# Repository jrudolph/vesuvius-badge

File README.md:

# Vesuvius First Word Badge - Hardware Design Files (for Kicad)

This repository contains the hardware design files for the Vesuvius First Word Badge badge that displays the first word found in burnt papyrus scrolls
analyzed for the [Vesuvius Challenge](https://scrollprize.substack.com/p/first-word-discovered-in-unopened).

Read more about the hardware of the badge in this [blog post](https://vesuvius.virtual-void.net/blog/2024/01/10/vesuvius-badge-hardware/). The Pico-based
firmware can be found in [vesuvius-badge-pico](https://github.com/jrudolph/vesuvius-badge-pico).

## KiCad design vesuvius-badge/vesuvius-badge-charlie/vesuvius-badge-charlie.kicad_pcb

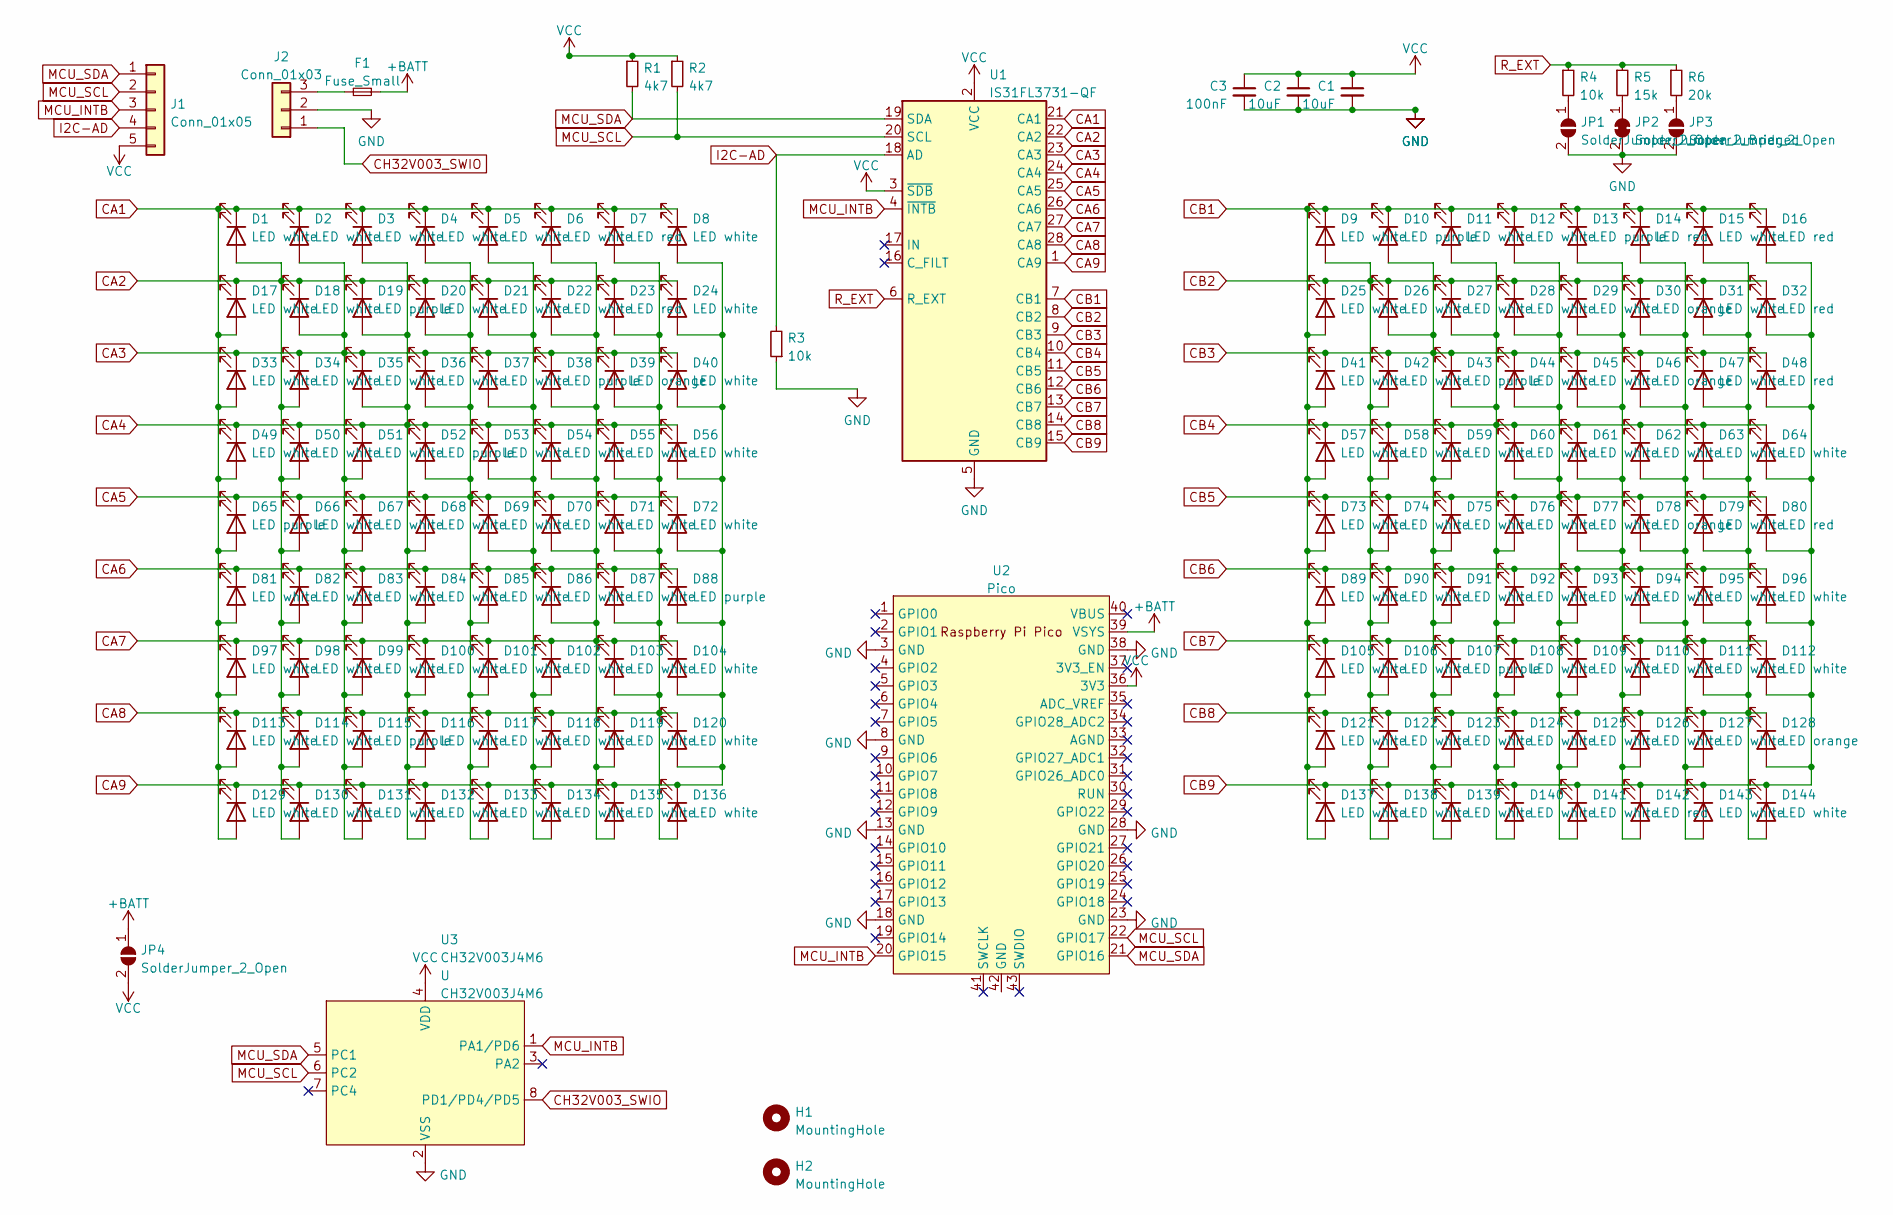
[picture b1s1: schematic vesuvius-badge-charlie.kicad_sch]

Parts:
C1, C2: 10uF; C_0402_1005Metric; LCSC C15525
C3: 100nF; C_0402_1005Metric; LCSC C1525
D1, D2, D3, D4, D5, D6, D8, D9, D11, D12, D15, D17, D18, D20, D21, D22, D24, D25, D26, D27, D28, D29, D31, D33, D34, D35, D36, D37, D40, D41, D42, D44, D45, D47, D49, D50, D51, D53, D54, D55, D56, D57, D58, D59, D60, D61, D62, D63, D64, D66, D67, D68, D69, D70, D71, D72, D73, D74, D75, D76, D77, D79, D81, D82, D83, D84, D85, D86, D87, D89, D90, D91, D92, D93, D94, D95, D96, D97, D98, D99, D100, D101, D102, D103, D104, D105, D106, D108, D109, D110, D111, D112, D113, D114, D116, D117, D118, D119, D120, D121, D122, D123, D124, D125, D126, D127, D129, D130, D131, D132, D133, D134, D135, D136, D137, D138, D139, D140, D141, D143, D144: LED white; LED_0402_1005Metric; LCSC C965796
D7, D14, D16, D23, D32, D48, D80, D142: LED red; LED_0402_1005Metric; LCSC C779449
D10, D13, D19, D38, D43, D52, D65, D88, D107, D115: LED purple; LED_0603_1608Metric; LCSC C7371898
D30, D39, D46, D78, D128: LED orange; LED_0402_1005Metric; LCSC C779448
F1: Fuse_Small; Fuse_0402_1005Metric; LCSC C136320
H1, H2: MountingHole; MountingHole_5.3mm_M5
J1: Conn_01x05; PinHeader_1x05_P2.54mm_Vertical
J2: Conn_01x03; PinHeader_1x03_P2.54mm_Vertical
JP1, JP3, JP4: SolderJumper_2_Open; SolderJumper-2_P1.3mm_Open_Pad1.0x1.5mm
JP2: SolderJumper_2_Bridged; SolderJumper-2_P1.3mm_Bridged_Pad1.0x1.5mm
R1, R2: 4k7; R_0603_1608Metric; LCSC C23162
R3, R4: 10k; R_0603_1608Metric; LCSC C25804
R5: 15k; R_0603_1608Metric; LCSC C22809
R6: 20k; R_0603_1608Metric; LCSC C4184
U1: IS31FL3731-QF; QFN-28-1EP_4x4mm_P0.4mm_EP2.3x2.3mm; LCSC C191206
U2: Pico; RPi_Pico_SMD
U3: CH32V003J4M6; SOP-8_3.9x4.9mm_P1.27mm

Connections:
+BATT: F1.2, JP4.1 (A), U2.39 (VSYS)
CA1: D1.1 (K), D2.1 (K), D3.1 (K), D4.1 (K), D5.1 (K), D6.1 (K), D7.1 (K), D8.1 (K), D17.2 (A), D33.2 (A), D49.2 (A), D65.2 (A), D81.2 (A), D97.2 (A), D113.2 (A), D129.2 (A), U1.21 (CA1)
CA2: D1.2 (A), D17.1 (K), D18.1 (K), D19.1 (K), D20.1 (K), D21.1 (K), D22.1 (K), D23.1 (K), D24.1 (K), D34.2 (A), D50.2 (A), D66.2 (A), D82.2 (A), D98.2 (A), D114.2 (A), D130.2 (A), U1.22 (CA2)
CA3: D2.2 (A), D18.2 (A), D33.1 (K), D34.1 (K), D35.1 (K), D36.1 (K), D37.1 (K), D38.1 (K), D39.1 (K), D40.1 (K), D51.2 (A), D67.2 (A), D83.2 (A), D99.2 (A), D115.2 (A), D131.2 (A), U1.23 (CA3)
CA4: D3.2 (A), D19.2 (A), D35.2 (A), D49.1 (K), D50.1 (K), D51.1 (K), D52.1 (K), D53.1 (K), D54.1 (K), D55.1 (K), D56.1 (K), D68.2 (A), D84.2 (A), D100.2 (A), D116.2 (A), D132.2 (A), U1.24 (CA4)
CA5: D4.2 (A), D20.2 (A), D36.2 (A), D52.2 (A), D65.1 (K), D66.1 (K), D67.1 (K), D68.1 (K), D69.1 (K), D70.1 (K), D71.1 (K), D72.1 (K), D85.2 (A), D101.2 (A), D117.2 (A), D133.2 (A), U1.25 (CA5)
CA6: D5.2 (A), D21.2 (A), D37.2 (A), D53.2 (A), D69.2 (A), D81.1 (K), D82.1 (K), D83.1 (K), D84.1 (K), D85.1 (K), D86.1 (K), D87.1 (K), D88.1 (K), D102.2 (A), D118.2 (A), D134.2 (A), U1.26 (CA6)
CA7: D6.2 (A), D22.2 (A), D38.2 (A), D54.2 (A), D70.2 (A), D86.2 (A), D97.1 (K), D98.1 (K), D99.1 (K), D100.1 (K), D101.1 (K), D102.1 (K), D103.1 (K), D104.1 (K), D119.2 (A), D135.2 (A), U1.27 (CA7)
CA8: D7.2 (A), D23.2 (A), D39.2 (A), D55.2 (A), D71.2 (A), D87.2 (A), D103.2 (A), D113.1 (K), D114.1 (K), D115.1 (K), D116.1 (K), D117.1 (K), D118.1 (K), D119.1 (K), D120.1 (K), D136.2 (A), U1.28 (CA8)
CA9: D8.2 (A), D24.2 (A), D40.2 (A), D56.2 (A), D72.2 (A), D88.2 (A), D104.2 (A), D120.2 (A), D129.1 (K), D130.1 (K), D131.1 (K), D132.1 (K), D133.1 (K), D134.1 (K), D135.1 (K), D136.1 (K), U1.1 (CA9)
CB1: D9.1 (K), D10.1 (K), D11.1 (K), D12.1 (K), D13.1 (K), D14.1 (K), D15.1 (K), D16.1 (K), D25.2 (A), D41.2 (A), D57.2 (A), D73.2 (A), D89.2 (A), D105.2 (A), D121.2 (A), D137.2 (A), U1.7 (CB1)
CB2: D9.2 (A), D25.1 (K), D26.1 (K), D27.1 (K), D28.1 (K), D29.1 (K), D30.1 (K), D31.1 (K), D32.1 (K), D42.2 (A), D58.2 (A), D74.2 (A), D90.2 (A), D106.2 (A), D122.2 (A), D138.2 (A), U1.8 (CB2)
CB3: D10.2 (A), D26.2 (A), D41.1 (K), D42.1 (K), D43.1 (K), D44.1 (K), D45.1 (K), D46.1 (K), D47.1 (K), D48.1 (K), D59.2 (A), D75.2 (A), D91.2 (A), D107.2 (A), D123.2 (A), D139.2 (A), U1.9 (CB3)
CB4: D11.2 (A), D27.2 (A), D43.2 (A), D57.1 (K), D58.1 (K), D59.1 (K), D60.1 (K), D61.1 (K), D62.1 (K), D63.1 (K), D64.1 (K), D76.2 (A), D92.2 (A), D108.2 (A), D124.2 (A), D140.2 (A), U1.10 (CB4)
CB5: D12.2 (A), D28.2 (A), D44.2 (A), D60.2 (A), D73.1 (K), D74.1 (K), D75.1 (K), D76.1 (K), D77.1 (K), D78.1 (K), D79.1 (K), D80.1 (K), D93.2 (A), D109.2 (A), D125.2 (A), D141.2 (A), U1.11 (CB5)
CB6: D13.2 (A), D29.2 (A), D45.2 (A), D61.2 (A), D77.2 (A), D89.1 (K), D90.1 (K), D91.1 (K), D92.1 (K), D93.1 (K), D94.1 (K), D95.1 (K), D96.1 (K), D110.2 (A), D126.2 (A), D142.2 (A), U1.12 (CB6)
CB7: D14.2 (A), D30.2 (A), D46.2 (A), D62.2 (A), D78.2 (A), D94.2 (A), D105.1 (K), D106.1 (K), D107.1 (K), D108.1 (K), D109.1 (K), D110.1 (K), D111.1 (K), D112.1 (K), D127.2 (A), D143.2 (A), U1.13 (CB7)
CB8: D15.2 (A), D31.2 (A), D47.2 (A), D63.2 (A), D79.2 (A), D95.2 (A), D111.2 (A), D121.1 (K), D122.1 (K), D123.1 (K), D124.1 (K), D125.1 (K), D126.1 (K), D127.1 (K), D128.1 (K), D144.2 (A), U1.14 (CB8)
CB9: D16.2 (A), D32.2 (A), D48.2 (A), D64.2 (A), D80.2 (A), D96.2 (A), D112.2 (A), D128.2 (A), D137.1 (K), D138.1 (K), D139.1 (K), D140.1 (K), D141.1 (K), D142.1 (K), D143.1 (K), D144.1 (K), U1.15 (CB9)
CH32V003_SWIO: J2.1, U3.8 (PD1/PD4/PD5)
GND: C1.2, C2.2, C3.2, J2.2, JP1.2 (B), JP2.2 (B), JP3.2 (B), R3.1, U1.5 (GND), U1.29 (GND), U2.3 (GND), U2.8 (GND), U2.13 (GND), U2.18 (GND), U2.23 (GND), U2.28 (GND), U2.38 (GND), U3.2 (VSS)
I2C-AD: J1.4, R3.2, U1.18 (AD)
MCU_INTB: J1.3, U1.4 (~INTB), U2.20 (GPIO15), U3.1 (PA1/PD6)
MCU_SCL: J1.2, R2.2, U1.20 (SCL), U2.22 (GPIO17), U3.6 (PC2)
MCU_SDA: J1.1, R1.2, U1.19 (SDA), U2.21 (GPIO16), U3.5 (PC1)
unnamed: F1.1, J2.3
unnamed: JP1.1 (A), R4.2
unnamed: JP2.1 (A), R5.2
unnamed: JP3.1 (A), R6.2
R_EXT: R4.1, R5.1, R6.1, U1.6 (R_EXT)
VCC: C1.1, C2.1, C3.1, J1.5, JP4.2 (B), R1.1, R2.1, U1.2 (VCC), U1.3 (~SDB), U2.36 (3V3), U3.4 (VDD)

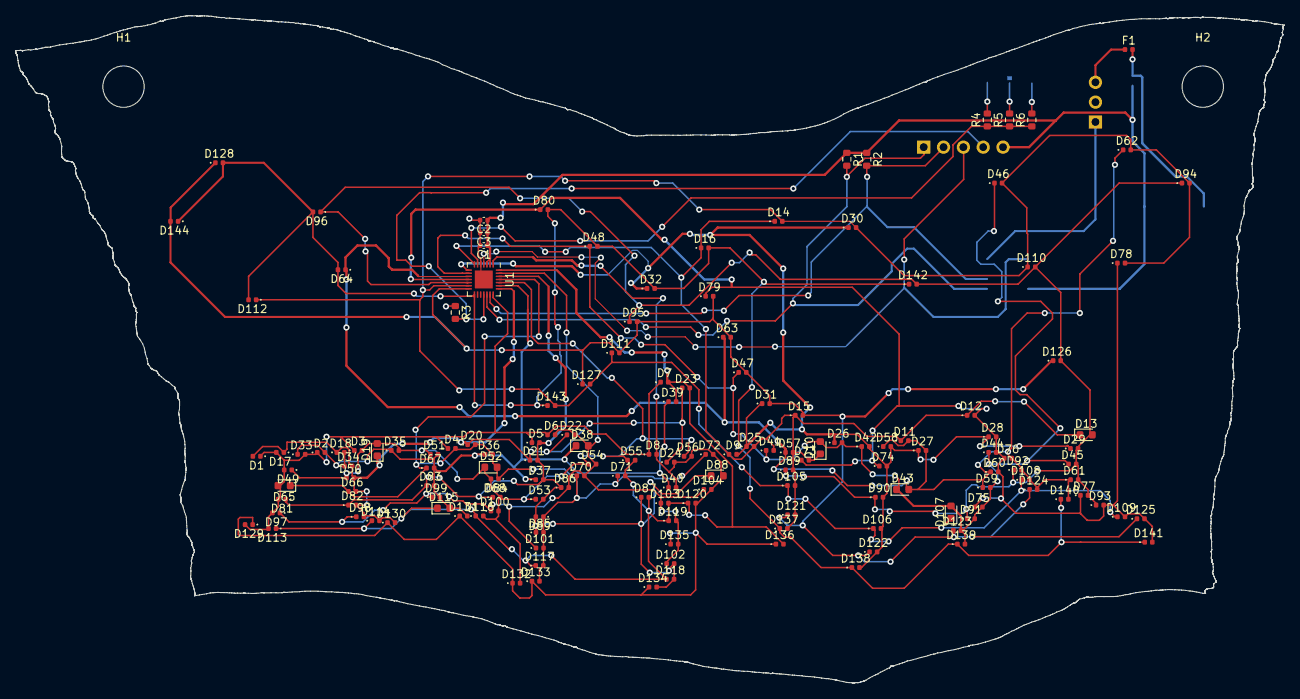
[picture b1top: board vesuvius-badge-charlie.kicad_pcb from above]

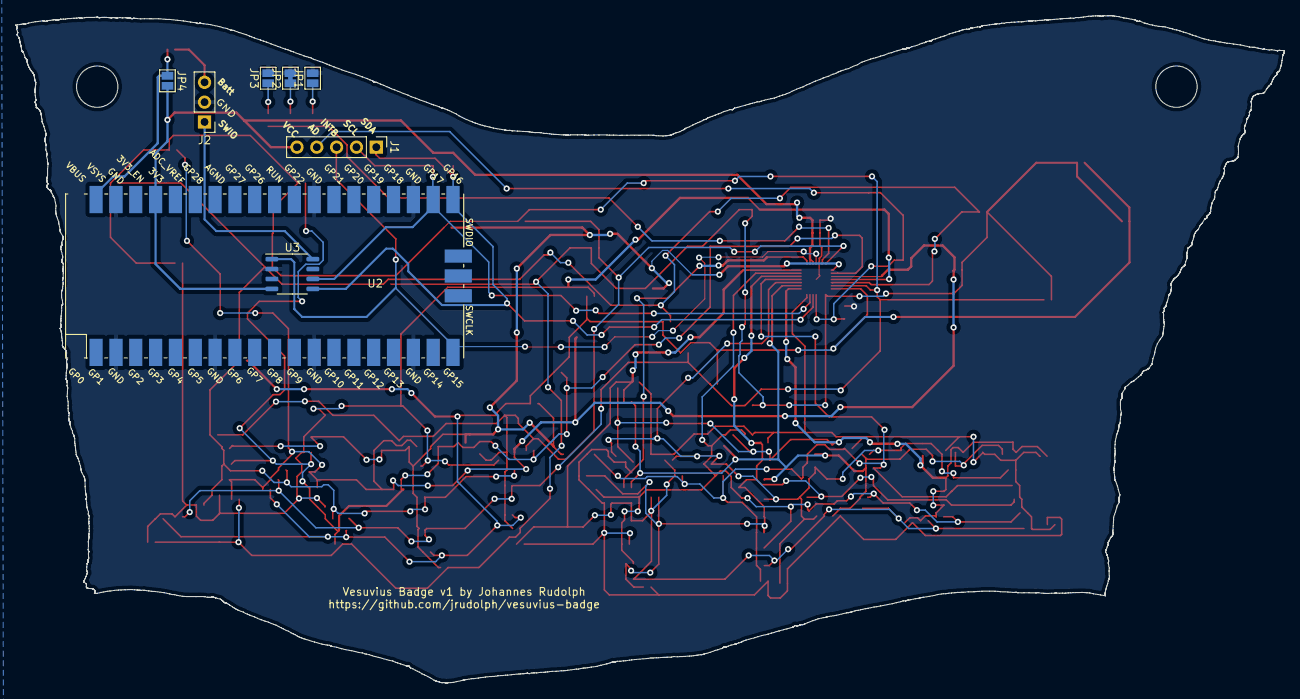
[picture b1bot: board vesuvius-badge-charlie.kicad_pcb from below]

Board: 2 copper layers, 162.5 x 85.5 mm, 165 parts (8 on the bottom side), 31 nets.

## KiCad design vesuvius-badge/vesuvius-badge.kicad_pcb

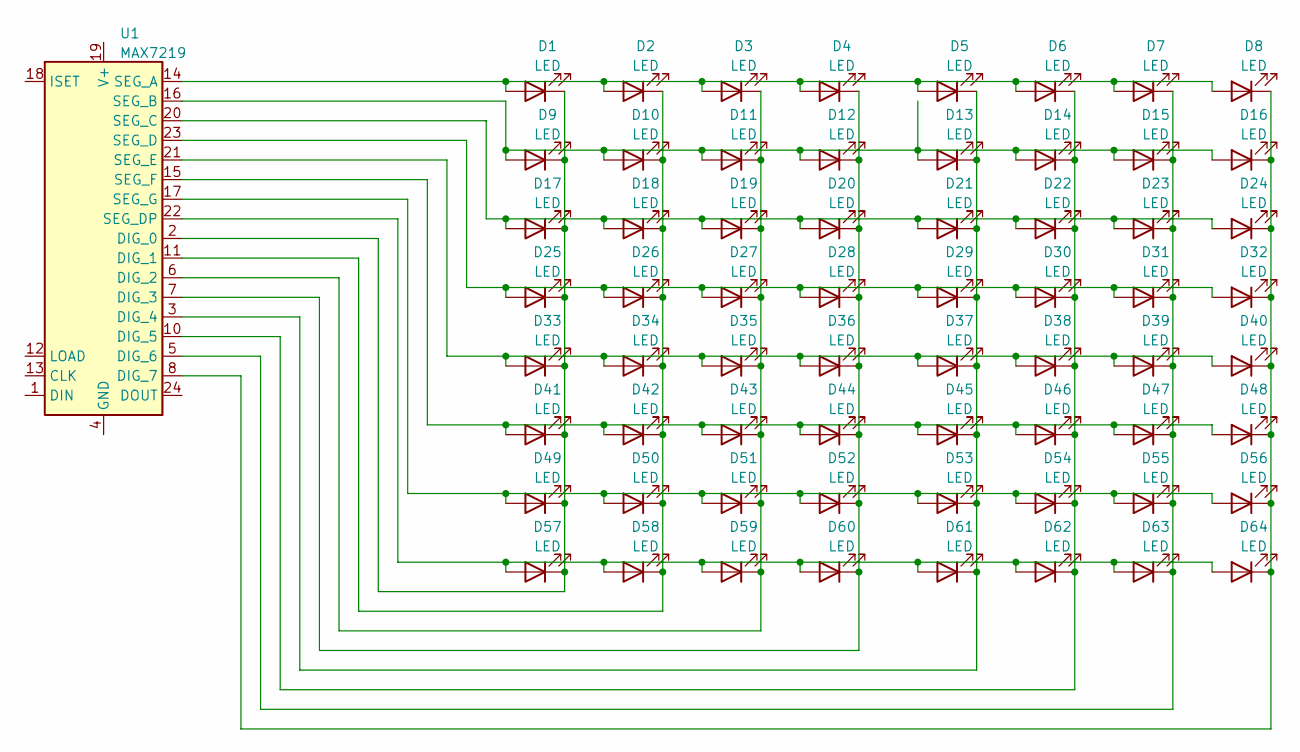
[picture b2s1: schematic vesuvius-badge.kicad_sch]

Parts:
D1, D2, D3, D4, D5, D6, D7, D8, D9, D10, D11, D12, D13, D14, D15, D16, D17, D18, D19, D20, D21, D22, D23, D24, D25, D26, D27, D28, D29, D30, D31, D32, D33, D34, D35, D36, D37, D38, D39, D40, D41, D42, D43, D44, D45, D46, D47, D48, D49, D50, D51, D52, D53, D54, D55, D56, D57, D58, D59, D60, D61, D62, D63, D64: LED; LED_0603_1608Metric
U1: MAX7219; SOP-24_7.5x15.4mm_P1.27mm

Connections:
unnamed: D1.1 (K), D9.1 (K), D17.1 (K), D25.1 (K), D33.1 (K), D41.1 (K), D49.1 (K), D57.1 (K), U1.2 (DIG_0)
unnamed: D1.2 (A), D2.2 (A), D3.2 (A), D4.2 (A), D5.2 (A), D6.2 (A), D7.2 (A), D8.2 (A), U1.14 (SEG_A)
unnamed: D2.1 (K), D10.1 (K), D18.1 (K), D26.1 (K), D34.1 (K), D42.1 (K), D50.1 (K), D58.1 (K), U1.11 (DIG_1)
unnamed: D9.2 (A), D10.2 (A), D11.2 (A), D12.2 (A), D13.2 (A), D14.2 (A), D15.2 (A), D16.2 (A), U1.16 (SEG_B)
unnamed: D3.1 (K), D11.1 (K), D19.1 (K), D27.1 (K), D35.1 (K), D43.1 (K), D51.1 (K), D59.1 (K), U1.6 (DIG_2)
unnamed: D4.1 (K), D12.1 (K), D20.1 (K), D28.1 (K), D36.1 (K), D44.1 (K), D52.1 (K), D60.1 (K), U1.7 (DIG_3)
unnamed: D5.1 (K), D13.1 (K), D21.1 (K), D29.1 (K), D37.1 (K), D45.1 (K), D53.1 (K), D61.1 (K), U1.3 (DIG_4)
unnamed: D6.1 (K), D14.1 (K), D22.1 (K), D30.1 (K), D38.1 (K), D46.1 (K), D54.1 (K), D62.1 (K), U1.10 (DIG_5)
unnamed: D7.1 (K), D15.1 (K), D23.1 (K), D31.1 (K), D39.1 (K), D47.1 (K), D55.1 (K), D63.1 (K), U1.5 (DIG_6)
unnamed: D8.1 (K), D16.1 (K), D24.1 (K), D32.1 (K), D40.1 (K), D48.1 (K), D56.1 (K), D64.1 (K), U1.8 (DIG_7)
unnamed: D17.2 (A), D18.2 (A), D19.2 (A), D20.2 (A), D21.2 (A), D22.2 (A), D23.2 (A), D24.2 (A), U1.20 (SEG_C)
unnamed: D25.2 (A), D26.2 (A), D27.2 (A), D28.2 (A), D29.2 (A), D30.2 (A), D31.2 (A), D32.2 (A), U1.23 (SEG_D)
unnamed: D33.2 (A), D34.2 (A), D35.2 (A), D36.2 (A), D37.2 (A), D38.2 (A), D39.2 (A), D40.2 (A), U1.21 (SEG_E)
unnamed: D41.2 (A), D42.2 (A), D43.2 (A), D44.2 (A), D45.2 (A), D46.2 (A), D47.2 (A), D48.2 (A), U1.15 (SEG_F)
unnamed: D49.2 (A), D50.2 (A), D51.2 (A), D52.2 (A), D53.2 (A), D54.2 (A), D55.2 (A), D56.2 (A), U1.17 (SEG_G)
unnamed: D57.2 (A), D58.2 (A), D59.2 (A), D60.2 (A), D61.2 (A), D62.2 (A), D63.2 (A), D64.2 (A), U1.22 (SEG_DP)
unnamed: U1.4 (GND), U1.9 (GND)

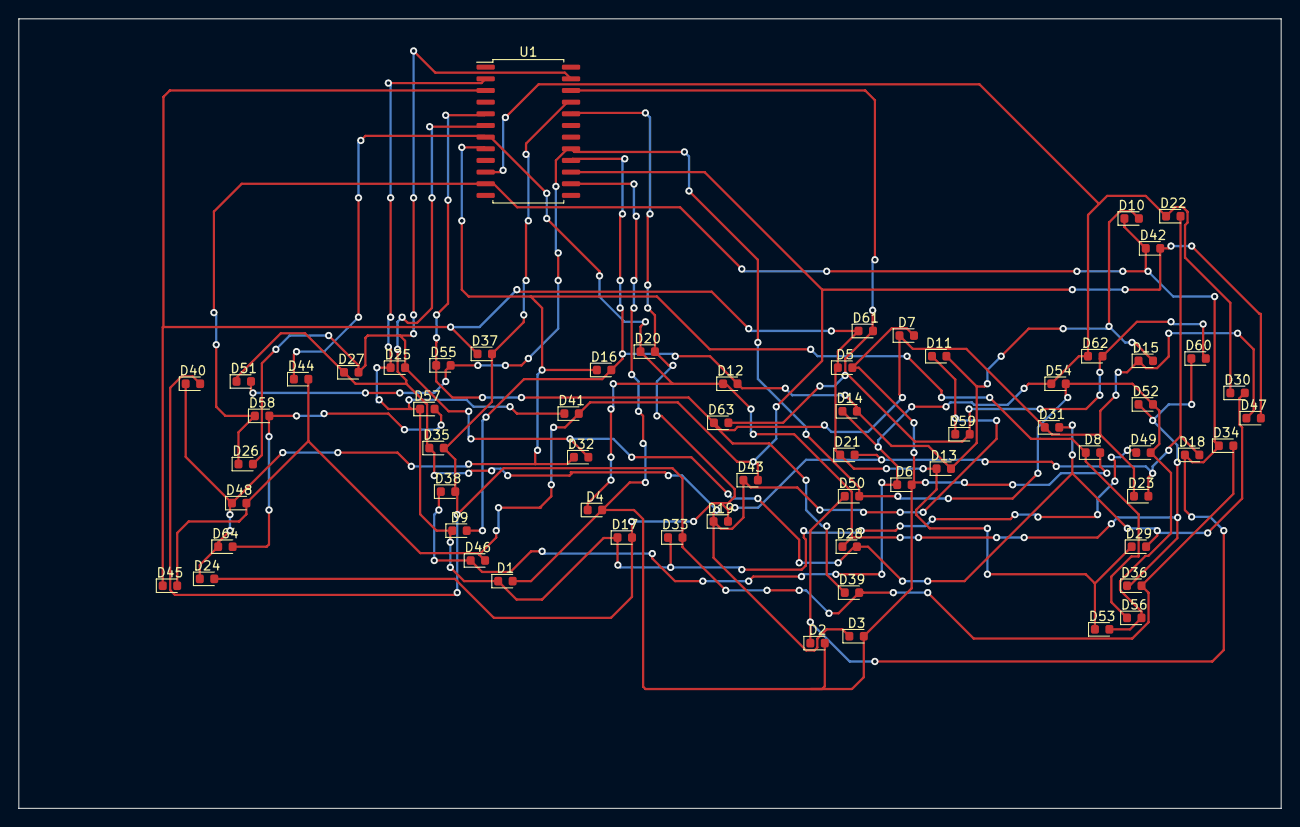
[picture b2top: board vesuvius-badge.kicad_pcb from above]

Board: 2 copper layers, 137.5 x 86.0 mm, 65 parts (0 on the bottom side), 17 nets.

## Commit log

2023-11-24 basic setup
2023-11-24 some routing done
2023-11-27 setup new badge based on IS31FL3731
2023-11-29 letters and vesuvius
2023-12-02 letters done, now the rest of the wiring
2023-12-02 routing mostly dnoe
2023-12-02 wiring done
2023-12-07 create wider tracks near the driver for long nets
2023-12-19 before applying purple diode footprint resize
2023-12-19 redo pcb after led footprint change
2023-12-20 finished functional parts
2023-12-27 final files and gerbers as submitted to production
2023-12-27 latest versions
2023-12-27 gerber screenshot teaser
2024-01-08 move some media files around
2024-01-08 small scala script to extract absolute positions from production files into C code
2024-01-08 latest changes
2024-04-28 as found
2024-04-28 cleanup
2024-04-28 move the real design to main directory, remove old design
2024-04-28 add some checklists
2024-04-28 add gitignore
2024-04-28 add v1 final schematics pdf
2024-04-29 add small readme
2024-04-29 add image for readme
2024-04-29 add another animation
